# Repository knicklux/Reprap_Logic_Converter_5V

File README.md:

# Reprap_Logic_Converter_5V
This small PCB can be used to make life with common Reprap Z_Probes easier by converting the 12V/24V sensor logic to 5V logic.

Steps:
 * read this README to the end
 * wiring
 * configure Marlin (pullup resistors)
 * test

Pins:

Hold the PCB so you can read the input numbers X4, X3 and X2.

X4: Sensor Interface
	Left: 	Signal
	Middle:	GND
	Right:	12V or 24V

X3: PCB Power supply
	Left:	GND
	Right:	12V or 24V

X2: 5V Logic Output
	Left:	GND
	Right:	5V logic Sensor output, pullup required

Wiring:

Always pay attention to pin assignment! 

1) Connect the Sensor to X4

2) Connect 12V or 24V from your PSU to X3

3) Connect X4 to your RAMPS/Rumba/Rambo (your printer's mainboard in general) Z_Min signal (s) and ground (-)

Marlin:

Enable Z-Endstop pullup in Configuration.h:
  #define ENDSTOPPULLUP_ZMIN

Test:

Better safe than sorry, test carefully and with care. Helpul commands: M119, M48

Thanks to the students at Kamaro Engineering who helped me with the design and improved it!

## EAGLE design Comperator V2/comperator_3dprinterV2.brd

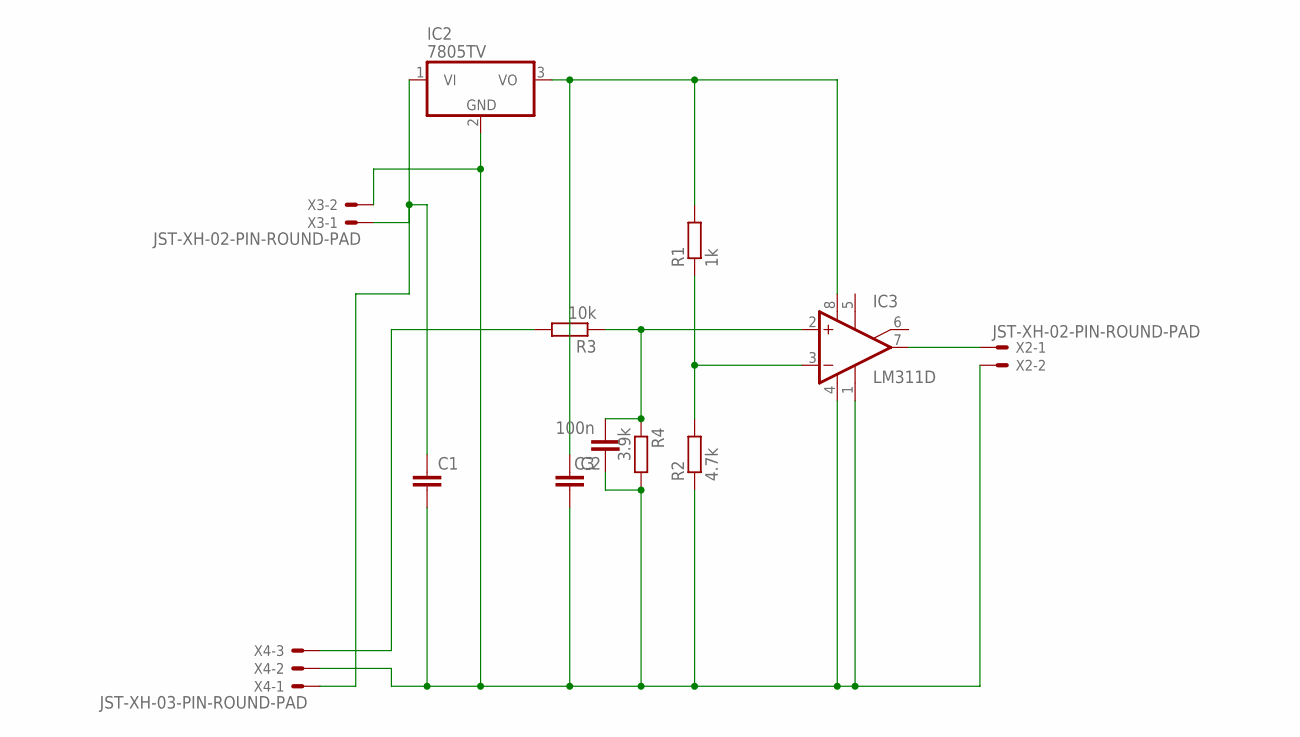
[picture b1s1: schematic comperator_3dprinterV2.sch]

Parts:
C1, C2: C2.5/2; C2.5-2
C3: 100n; C2.5-2
IC2: 7805TV; TO220V
IC3: LM311D; SO08
R1: 1k; 0207/7
R2: 4.7k; 0207/7
R3: 10k; 0207/7
R4: 3.9k; 0207/7
X2, X3: JST-XH-02-PIN-ROUND-PAD; JST-XH-02-PACKAGE-ROUND-PAD
X4: JST-XH-03-PIN-ROUND-PAD; JST-XH-03-PACKAGE-ROUND-PAD

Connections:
GND: C1.2, C2.2, C3.1, IC2.2 (GND), IC3.1 (GND), IC3.4 (V-), R2.1, R4.2, X2.2, X3.2, X4.2
unnamed: IC3.7 (OUT), X2.1
unnamed: R3.2, X4.3
unnamed: C2.1, IC2.3 (VO), IC3.8 (V+), R1.2
unnamed: C3.2, IC3.2 (+IN), R3.1, R4.1
unnamed: IC3.3 (-IN), R1.1, R2.2
VCC: C1.1, IC2.1 (VI), X3.1, X4.1

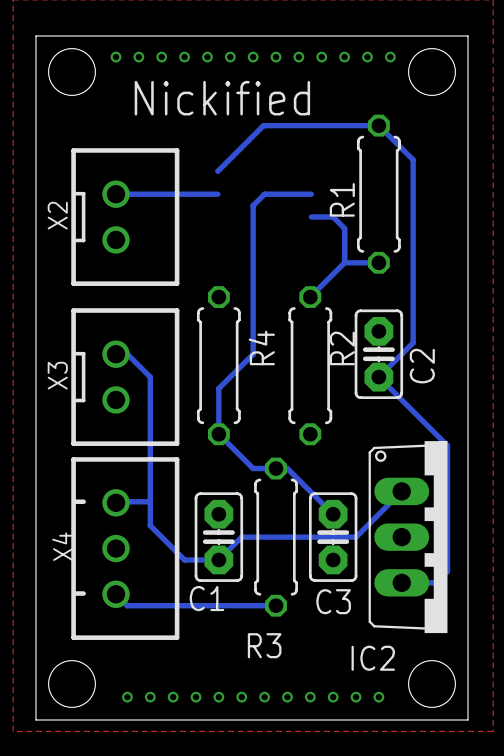
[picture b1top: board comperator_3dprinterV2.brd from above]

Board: 2 copper layers, 24.0 x 38.0 mm, 12 parts (1 on the bottom side), 7 nets.

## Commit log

2017-09-05 Release
2017-09-05 Improved README
2017-09-05 Update README.md
    added credits
2017-09-05 added gitignore
